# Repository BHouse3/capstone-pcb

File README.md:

# capstone-pcb

All files and documentation for PCB integration.

## Timeline

01/12/2026 - Created project repo and initial hierarchical KiCad structure. Found DFRobot's rp2350 module footprint.

01/13/2026 - Ethan created symbol for rp2350 module.

01/14/2026 - Created fuel gauge schematic with LC709203FQH-01TWG. Evaluating charging and voltage conversion methodology. 

01/15/2026 - Redesign of entire power subsystem. Utilizing TP4057 charger on board RP2350 module. DW01A + FS8205A protection circuitry. TPS61023 5V boost converter. BQ27441-G1 fuel gauge. Minimizes cost and number of components in power system. Ethan created L1 schematic with labels and wires for the symbol created on 01/13/2026. The symbol was also edited to correct labeling errors.

01/17/2026 - Power schematic starting point based on datasheet implementations. Will work to further verify. Changed MCU labels to global labels.

01/20/2026 - UI schematic finished. External connector symbols added. Hierarchical label issue. Washout detection schematic finished. Motor schematic finished.

01/22/2026 - Fixed critical polarity issue on flyback diodes. Hierarchical label assignment. Added missing I2C labels on power system

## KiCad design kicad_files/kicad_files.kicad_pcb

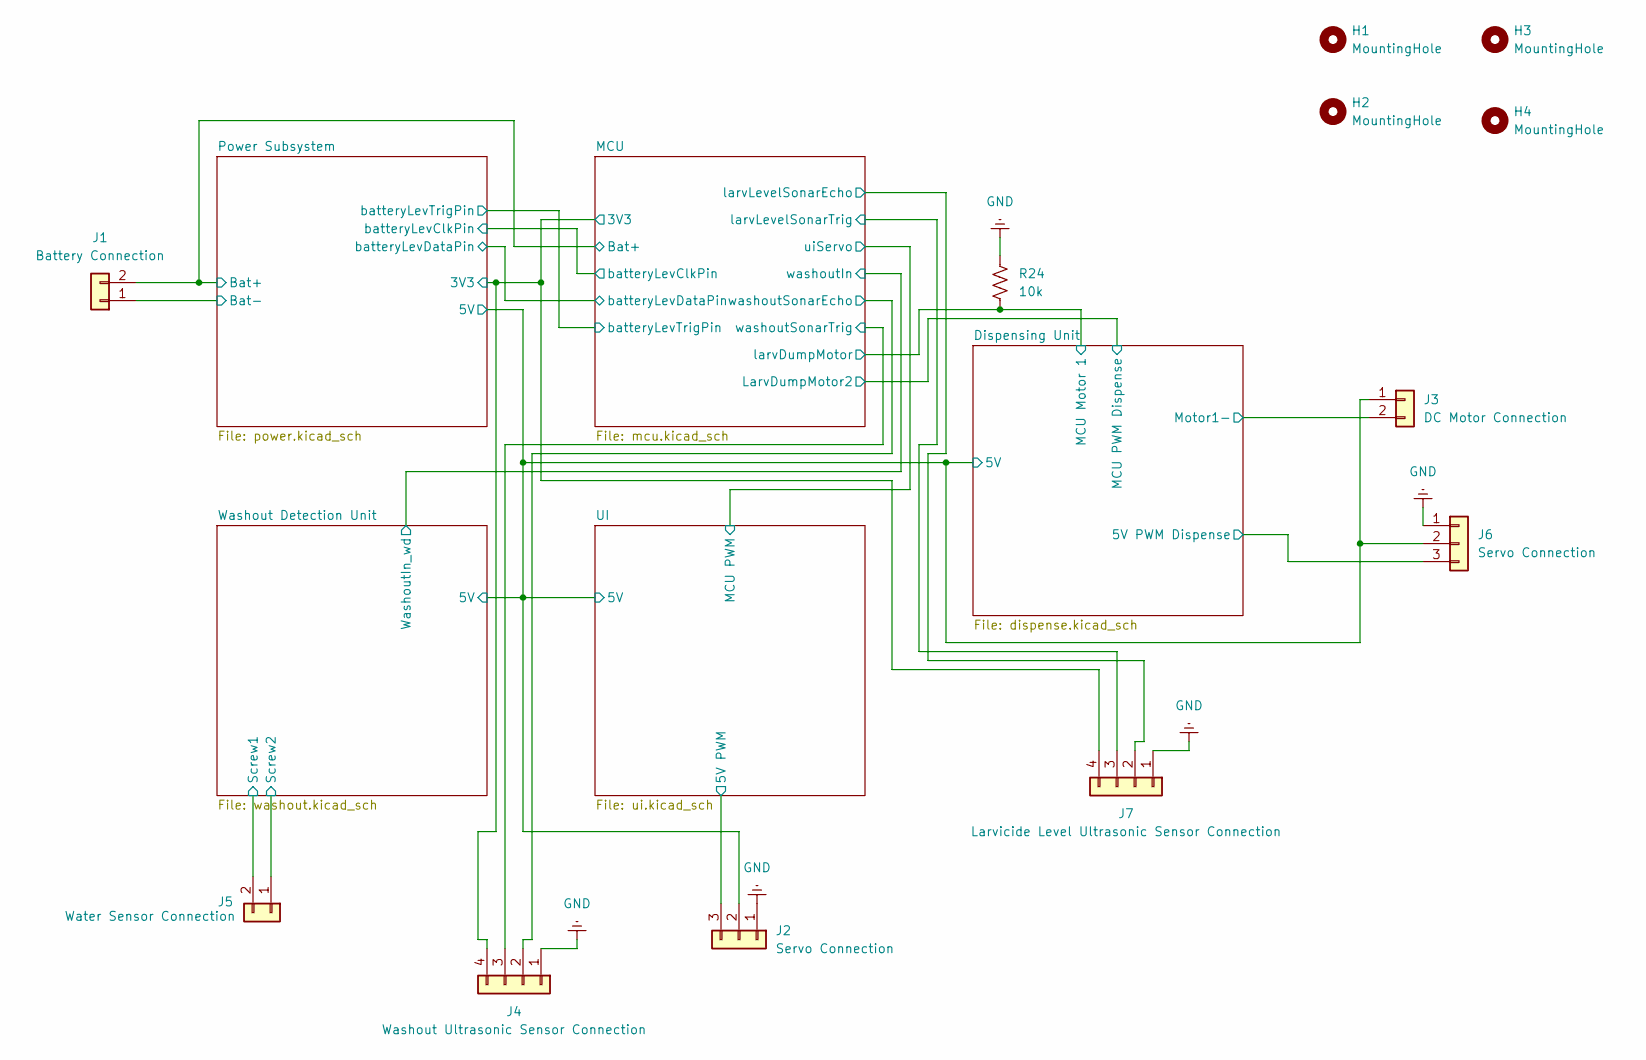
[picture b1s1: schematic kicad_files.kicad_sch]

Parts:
H1, H2, H3, H4: MountingHole; MountingHole_3.2mm_M3
J1: Battery Connection; JST_VH_B2P-VH_1x02_P3.96mm_Vertical
J2, J6: Servo Connection; PinHeader_1x03_P2.54mm_Vertical
J3: DC Motor Connection; JST_XH_B2B-XH-A_1x02_P2.50mm_Vertical
J4: Washout Ultrasonic Sensor Connection; JST_XH_B4B-XH-A_1x04_P2.50mm_Vertical
J5: Water Sensor Connection; JST_XH_B2B-XH-A_1x02_P2.50mm_Vertical
J7: Larvicide Level Ultrasonic Sensor Connection; JST_XH_B4B-XH-A_1x04_P2.50mm_Vertical
R24: 10k; R_1206_3216Metric_Pad1.30x1.75mm_HandSolder

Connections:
/Dispensing Unit/5V: J2.2, J3.1, J6.2; also elsewhere on the board
/Dispensing Unit/5V PWM Dispense: J6.3; also elsewhere on the board
/Dispensing Unit/MCU Motor 1: R24.2; also elsewhere on the board
/Dispensing Unit/Motor1-: J3.2; also elsewhere on the board
/MCU/3V3: J4.4, J7.4; also elsewhere on the board
/MCU/Bat+: J1.2; also elsewhere on the board
/MCU/larvLevelSonarEcho: J7.2; also elsewhere on the board
/MCU/larvLevelSonarTrig: J7.3; also elsewhere on the board
/MCU/washoutSonarEcho: J4.2; also elsewhere on the board
/MCU/washoutSonarTrig: J4.3; also elsewhere on the board
/Power Subsystem/Bat-: J1.1; also elsewhere on the board
/UI/5V PWM: J2.3; also elsewhere on the board
/Washout Detection Unit/Screw1: J5.2; also elsewhere on the board
/Washout Detection Unit/Screw2: J5.1; also elsewhere on the board
GND: J2.1, J4.1, J6.1, J7.1, R24.1; also elsewhere on the board

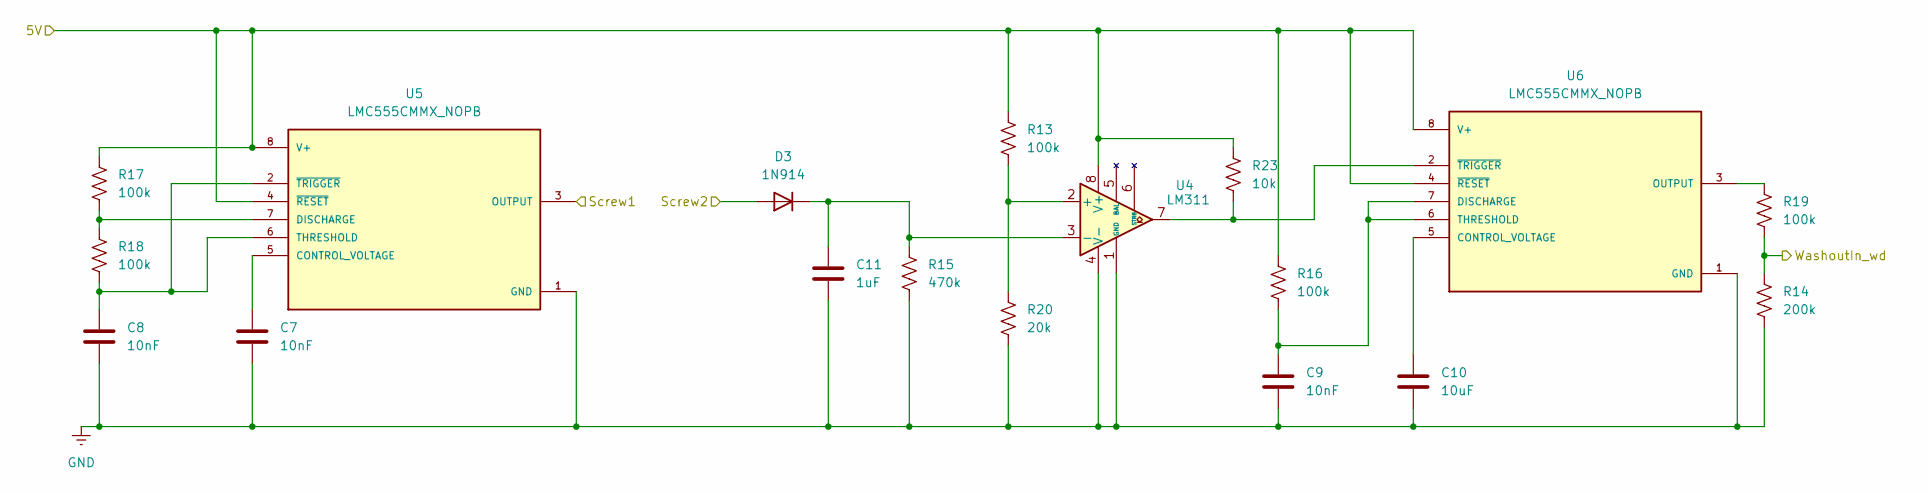
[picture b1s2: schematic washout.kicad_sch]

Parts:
C7, C8, C9: 10nF; C_1206_3216Metric_Pad1.33x1.80mm_HandSolder
C10: 10uF; C_1206_3216Metric_Pad1.33x1.80mm_HandSolder
C11: 1uF; C_1206_3216Metric_Pad1.33x1.80mm_HandSolder
D3: 1N914; D_DO-35_SOD27_P7.62mm_Horizontal
R13, R16, R17, R18, R19: 100k; R_1206_3216Metric_Pad1.30x1.75mm_HandSolder
R14: 200k; R_1206_3216Metric_Pad1.30x1.75mm_HandSolder
R15: 470k; R_1206_3216Metric_Pad1.30x1.75mm_HandSolder
R20: 20k; R_1206_3216Metric_Pad1.30x1.75mm_HandSolder
R23: 10k; R_1206_3216Metric_Pad1.30x1.75mm_HandSolder
U4: LM311; D8
U5, U6: LMC555CMMX_NOPB; D0008A_M; PARTREV M

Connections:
/Dispensing Unit/5V: R13.1, R16.1, R17.1, R23.1, U4.8 (V+), U5.4 (~RESET), U5.8 (V+), U6.4 (~RESET), U6.8 (V+); also elsewhere on the board
/MCU/washoutIn: R14.1, R19.2; also elsewhere on the board
/Washout Detection Unit/Screw1: U5.3 (OUTPUT); also elsewhere on the board
/Washout Detection Unit/Screw2: D3.2 (A); also elsewhere on the board
GND: C7.2, C8.2, C9.2, C10.2, C11.2, R14.2, R15.2, R20.2, U4.1 (GND), U4.4 (V-), U5.1 (GND), U6.1 (GND); also elsewhere on the board
unnamed: C11.1, D3.1 (K), R15.1, U4.3 (-)
unnamed: R13.2, R20.1, U4.2 (+)
unnamed: C7.1, U5.5 (CONTROL_VOLTAGE)
unnamed: R17.2, R18.1, U5.7 (DISCHARGE)
unnamed: C8.1, R18.2, U5.2 (~TRIGGER), U5.6 (THRESHOLD)
unnamed: C10.1, U6.5 (CONTROL_VOLTAGE)
unnamed: C9.1, R16.2, U6.6 (THRESHOLD), U6.7 (DISCHARGE)
unnamed: R19.1, U6.3 (OUTPUT)
unnamed: R23.2, U4.7, U6.2 (~TRIGGER)

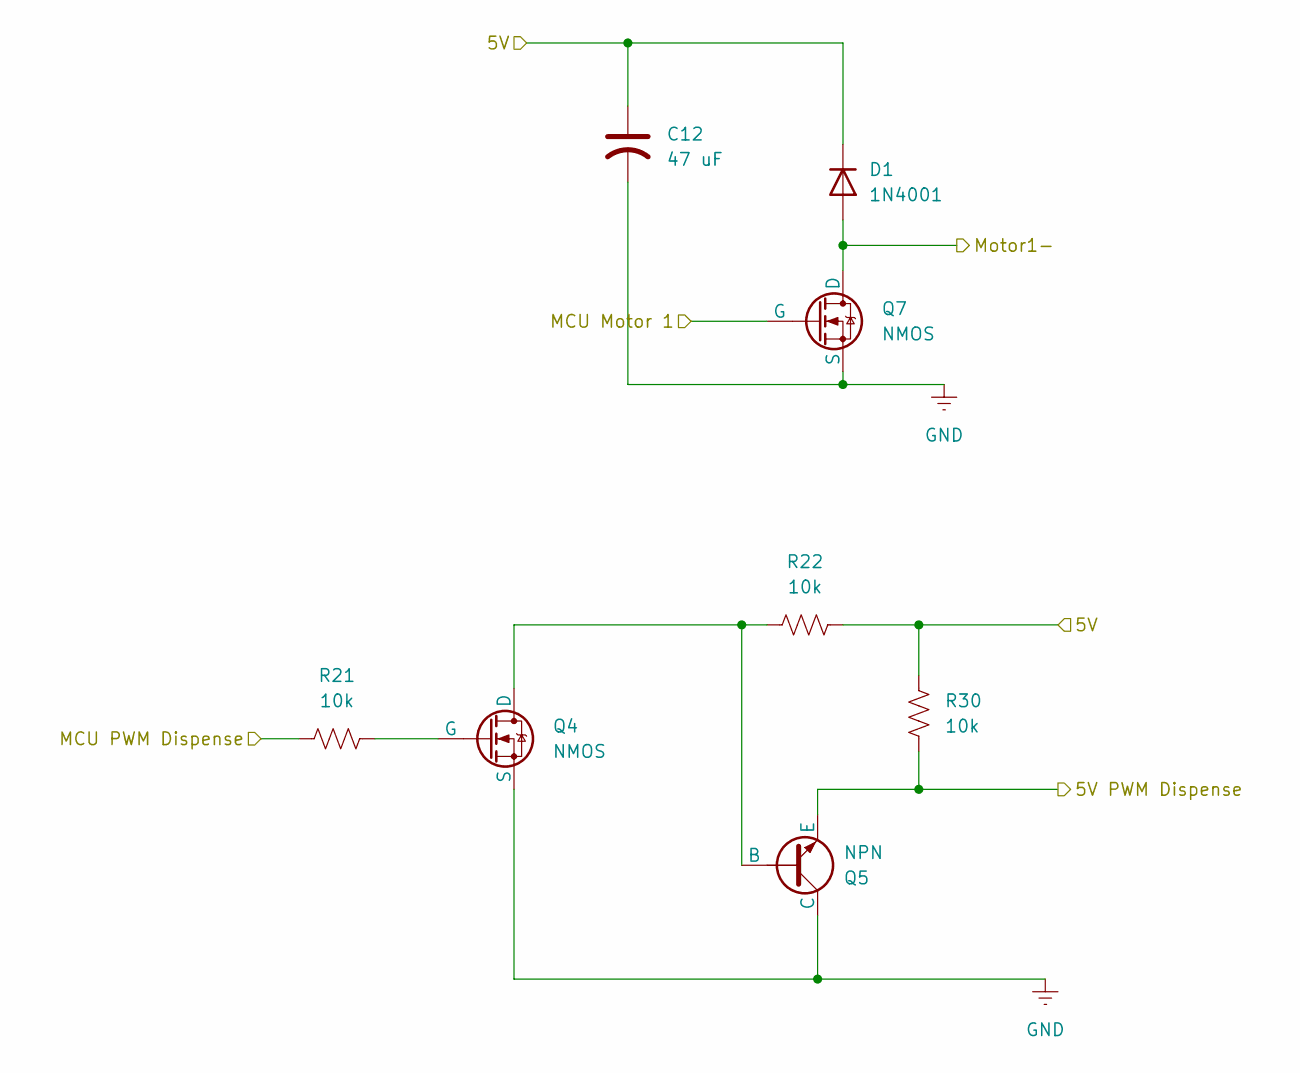
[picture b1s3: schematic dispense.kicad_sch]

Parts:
C12: 47 uF; CP_Radial_D5.0mm_P2.00mm
D1: 1N4001; D_DO-41_SOD81_P10.16mm_Horizontal
Q4: NMOS; SOT-323_SC-70
Q5: NPN; TSOT-23
Q7: NMOS; SOT-23-3
R21, R22, R30: 10k; R_1206_3216Metric_Pad1.30x1.75mm_HandSolder

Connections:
/Dispensing Unit/5V: C12.1, D1.1 (K), R22.1, R30.1; also elsewhere on the board
/Dispensing Unit/5V PWM Dispense: Q5.3 (E), R30.2; also elsewhere on the board
/Dispensing Unit/MCU Motor 1: Q7.2 (G); also elsewhere on the board
/Dispensing Unit/MCU PWM Dispense: R21.2; also elsewhere on the board
/Dispensing Unit/Motor1-: D1.2 (A), Q7.1 (D); also elsewhere on the board
GND: C12.2, Q4.3 (S), Q5.1 (C), Q7.3 (S); also elsewhere on the board
unnamed: Q4.1 (D), Q5.2 (B), R22.2
unnamed: Q4.2 (G), R21.1

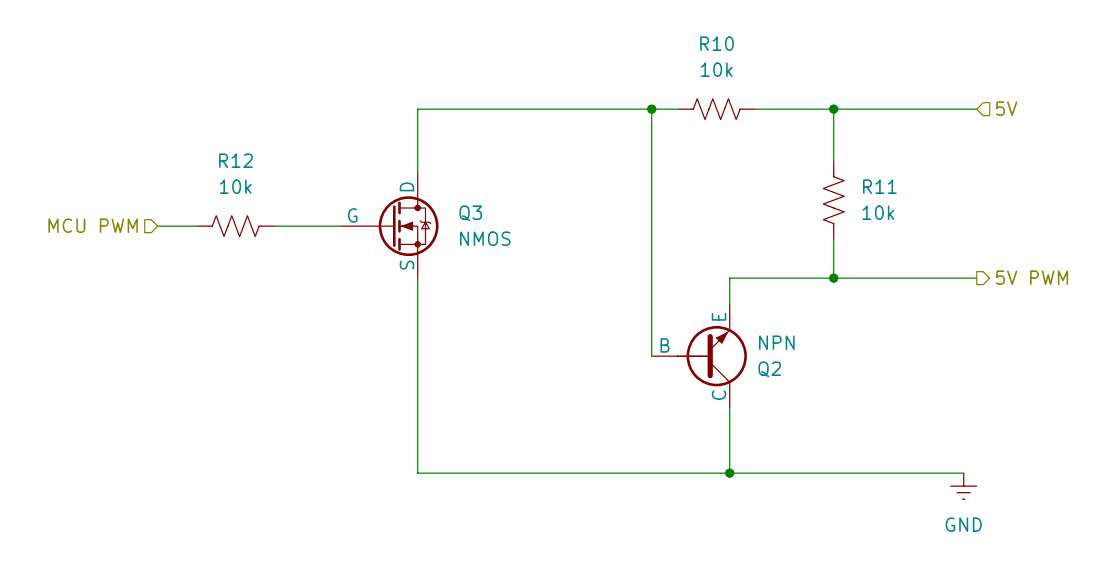
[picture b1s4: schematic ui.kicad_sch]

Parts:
Q2: NPN; TSOT-23
Q3: NMOS; SOT-323_SC-70
R10, R11, R12: 10k; R_1206_3216Metric_Pad1.30x1.75mm_HandSolder

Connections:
/Dispensing Unit/5V: R10.1, R11.1; also elsewhere on the board
/MCU/uiServo: R12.2; also elsewhere on the board
/UI/5V PWM: Q2.3 (E), R11.2; also elsewhere on the board
GND: Q2.1 (C), Q3.3 (S); also elsewhere on the board
unnamed: Q2.2 (B), Q3.1 (D), R10.2
unnamed: Q3.2 (G), R12.1

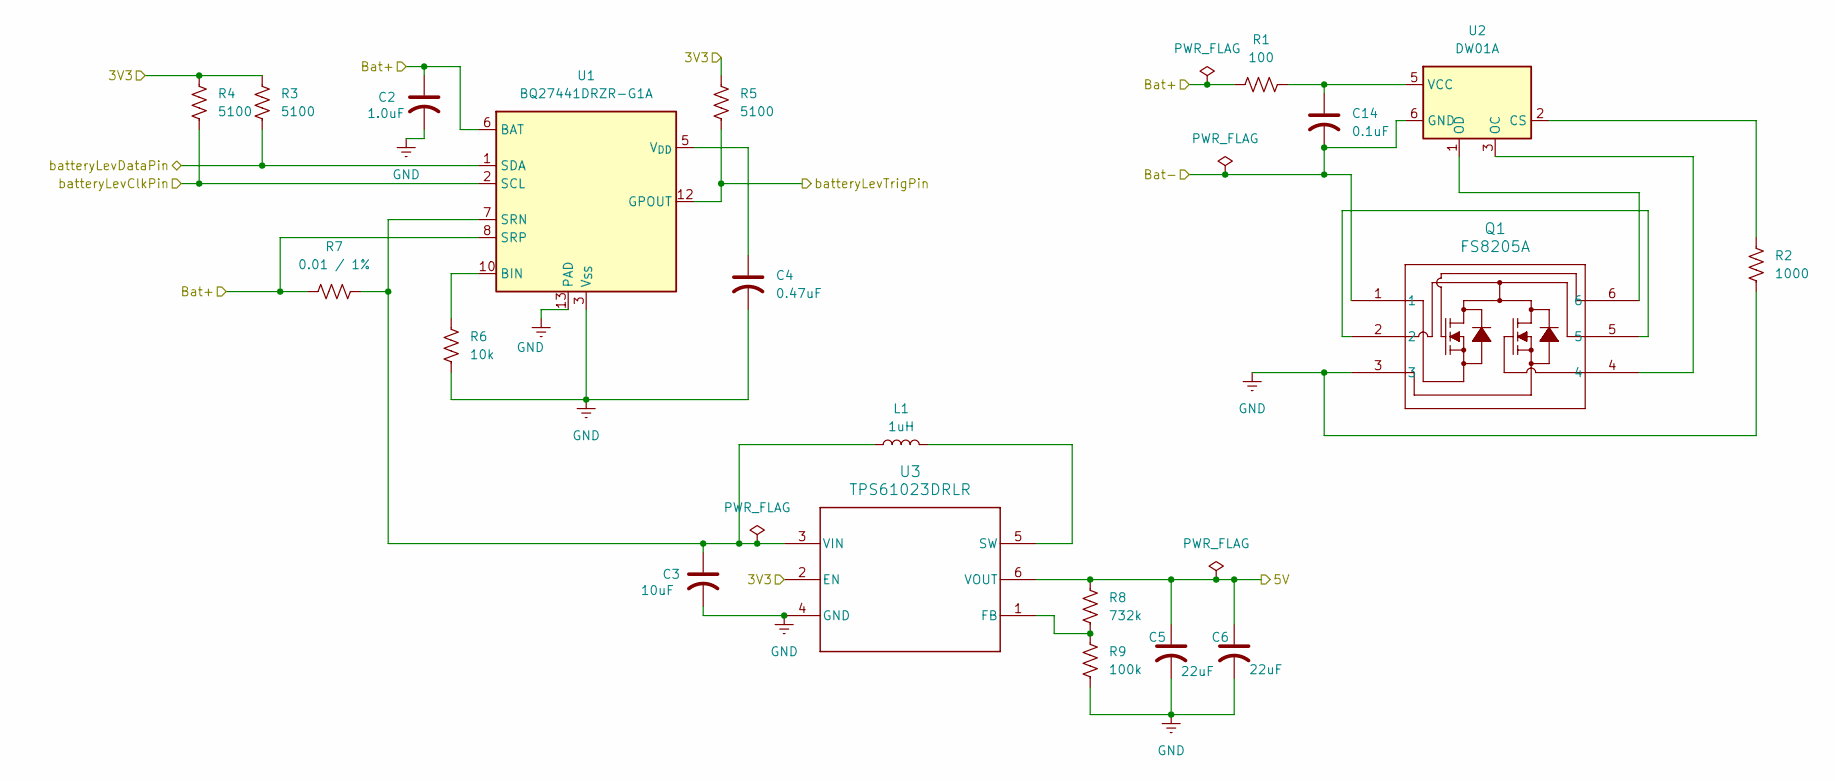
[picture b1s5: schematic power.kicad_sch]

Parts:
C2: 1.0uF; C_1206_3216Metric_Pad1.33x1.80mm_HandSolder
C3: 10uF; C_1206_3216Metric_Pad1.33x1.80mm_HandSolder
C4: 0.47uF; C_1206_3216Metric_Pad1.33x1.80mm_HandSolder
C5, C6: 22uF; CP_Radial_D5.0mm_P2.00mm
C14: 0.1uF; C_1206_3216Metric_Pad1.33x1.80mm_HandSolder
L1: 1uH; L_1008_2520Metric_Pad1.43x2.20mm_HandSolder
Q1: FS8205A; SOT-23-6L_TCP
R1: 100; R_1206_3216Metric_Pad1.30x1.75mm_HandSolder
R2: 1000; R_1206_3216Metric_Pad1.30x1.75mm_HandSolder
R3, R4, R5: 5100; R_1206_3216Metric_Pad1.30x1.75mm_HandSolder
R6: 10k; R_1206_3216Metric_Pad1.30x1.75mm_HandSolder
R7: 0.01 / 1%; R_1206_3216Metric_Pad1.30x1.75mm_HandSolder
R8: 732k; R_1206_3216Metric_Pad1.30x1.75mm_HandSolder
R9: 100k; R_1206_3216Metric_Pad1.30x1.75mm_HandSolder
U1: BQ27441DRZR-G1A; Texas_S-PDSO-N12
U2: DW01A; SOT-23-6
U3: TPS61023DRLR; DRL0006A

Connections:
/Dispensing Unit/5V: C5.1, C6.1, R8.1, U3.6 (VOUT); also elsewhere on the board
/MCU/3V3: R3.1, R4.1, R5.1, U3.2 (EN); also elsewhere on the board
/MCU/Bat+: C2.1, R1.2, R7.2, U1.6 (BAT), U1.8 (SRP); also elsewhere on the board
/MCU/batteryLevClkPin: R4.2, U1.2 (SCL); also elsewhere on the board
/MCU/batteryLevDataPin: R3.2, U1.1 (SDA); also elsewhere on the board
/MCU/batteryLevTrigPin: R5.2, U1.12 (GPOUT); also elsewhere on the board
/Power Subsystem/Bat-: C14.2, Q1.1, U2.6 (GND); also elsewhere on the board
GND: C2.2, C3.2, C4.2, C5.2, C6.2, Q1.3, R2.2, R6.2, R9.2, U1.3 (V_{SS}), U1.13 (PAD), U3.4 (GND); also elsewhere on the board
unnamed: Q1.2, Q1.5
unnamed: R6.1, U1.10 (BIN)
unnamed: C3.1, L1.1, R7.1, U1.7 (SRN), U3.3 (VIN)
unnamed: C4.1, U1.5 (V_{DD})
unnamed: R2.1, U2.2 (CS)
unnamed: Q1.4, U2.3 (OC)
unnamed: Q1.6, U2.1 (OD)
unnamed: C14.1, R1.1, U2.5 (VCC)
unnamed: R8.2, R9.1, U3.1 (FB)
unnamed: L1.2, U3.5 (SW)

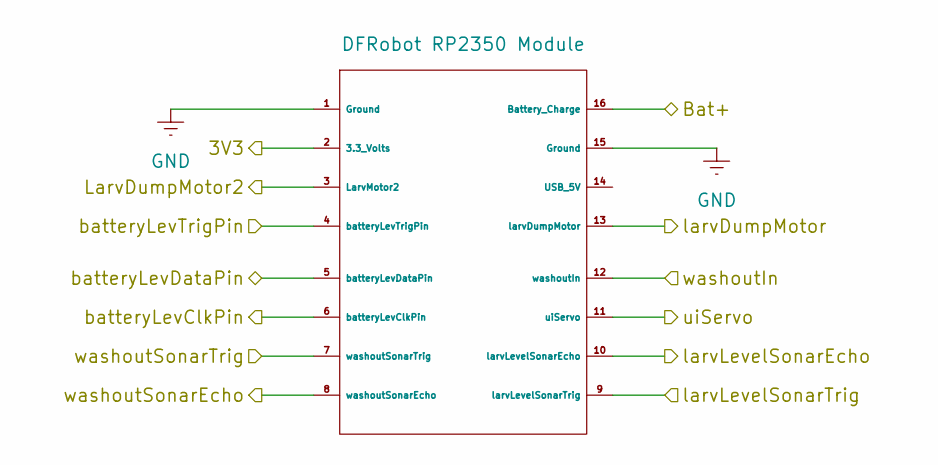
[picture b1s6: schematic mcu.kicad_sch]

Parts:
.1: DFRobot RP2350 Module; DFR1188-DIP

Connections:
unnamed: .1.1 (Ground), .1.15 (Ground)

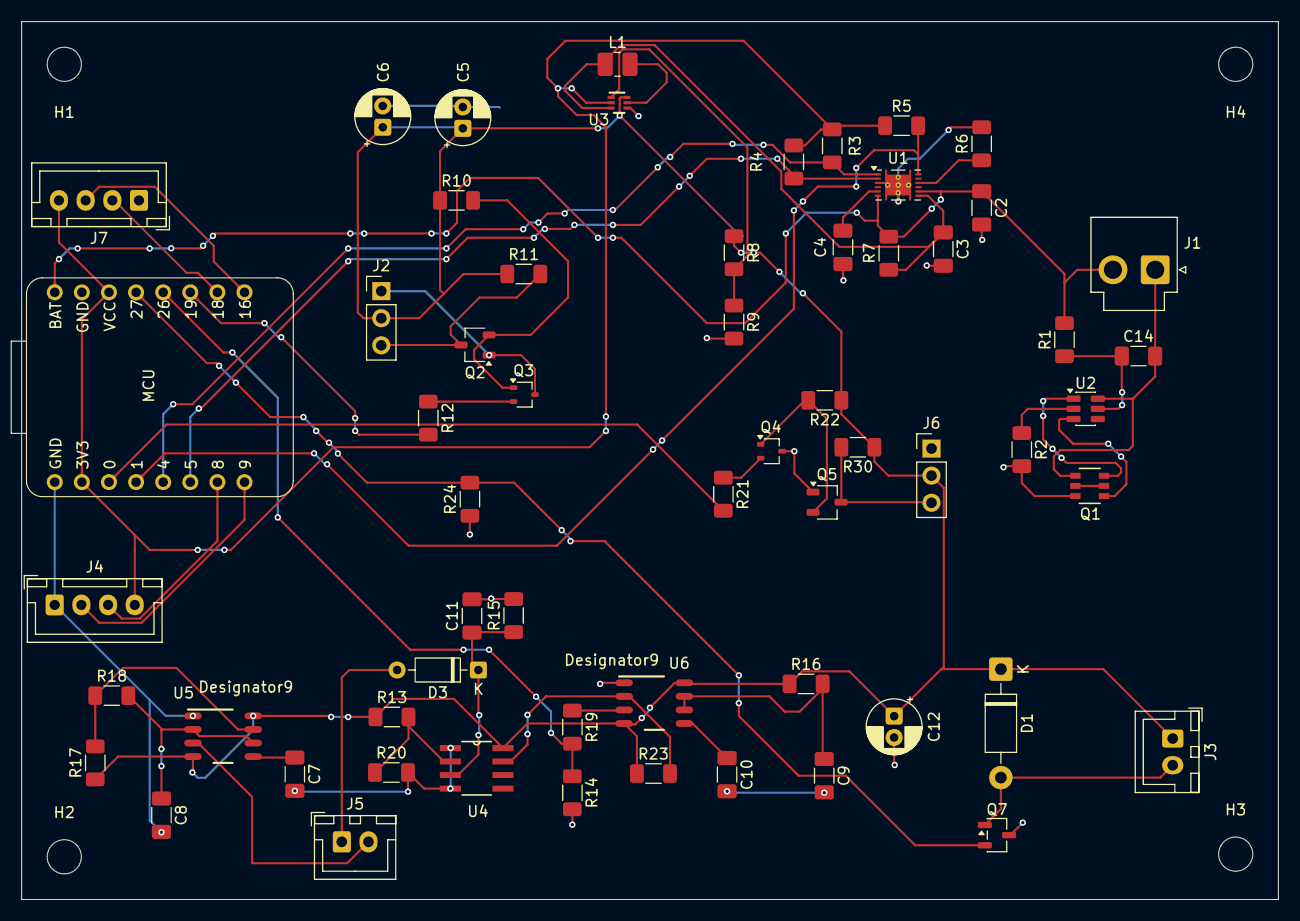
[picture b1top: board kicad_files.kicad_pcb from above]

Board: 2 copper layers, 117.8 x 82.2 mm, 64 parts (0 on the bottom side), 44 nets.

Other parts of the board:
MCU: DFRobot RP2350 Module; DFR1188-DIP

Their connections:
/Dispensing Unit/MCU Motor 1: MCU.13 (larvDumpMotor); also elsewhere on the board
/Dispensing Unit/MCU PWM Dispense: MCU.3 (LarvMotor2); also elsewhere on the board
/MCU/3V3: MCU.2 (3.3_Volts); also elsewhere on the board
/MCU/Bat+: MCU.16 (Battery_Charge); also elsewhere on the board
/MCU/batteryLevClkPin: MCU.6 (batteryLevClkPin); also elsewhere on the board
/MCU/batteryLevDataPin: MCU.5 (batteryLevDataPin); also elsewhere on the board
/MCU/batteryLevTrigPin: MCU.4 (batteryLevTrigPin); also elsewhere on the board
/MCU/larvLevelSonarEcho: MCU.10 (larvLevelSonarEcho); also elsewhere on the board
/MCU/larvLevelSonarTrig: MCU.9 (larvLevelSonarTrig); also elsewhere on the board
/MCU/uiServo: MCU.11 (uiServo); also elsewhere on the board
/MCU/washoutIn: MCU.12 (washoutIn); also elsewhere on the board
/MCU/washoutSonarEcho: MCU.8 (washoutSonarEcho); also elsewhere on the board
/MCU/washoutSonarTrig: MCU.7 (washoutSonarTrig); also elsewhere on the board
GND: MCU.1 (Ground), MCU.15 (Ground); also elsewhere on the board

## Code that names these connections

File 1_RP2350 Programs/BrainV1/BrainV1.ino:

//Project Name: Drain Defenders Processor Code
//Author: Ethan Conrad
//Reason: Control Drain Defenders Device
//Class: EE/CPE 490/491
//History: 10/30/2025 - Start Date
//         11/03/2025 - Adjusted pin definitions to match RP2350 actual pin layout, changed washoutIn to be a
//                      a digital input instead of analog to allow for interrupt usage, and added UI servo motor
//                      logic to work with one servo instead of two, and added servoCheck function to check
//                      servo states for the "both" state
//         11/04/2025 - Asjusted pin definitions to allow battery interrrupt sense to have I2C compatibility
//         11/10/2025 - Changed larvDumpMotor to larvDumpMotor due to realzing the RP2350 pins cannot supply in
//                      rush current needed to turn motor sufficiently. Then updated all code relevant to motor
//                      to digital commands to support MOSFET circuit logic
//         11/11/2025 - Adjusted duration of the low power sleep to be 5 minutes or 300000 ms
//         11/24/2025 - Changed Washout Sensor Interupt to falling edge based on results from testing script
//         12/02/2025 - Included Adafuit library and associated code/logic to enable I2C communication with Power
//                      Distribution subsystem
//         12/03/2025 - B.H.: Added I2C initialization and LC709203F/interrupt communication
//         12/08/2025 - added in set clock and data initialization code to fix I2C errors
//
//Purpose: To create a program that can be used to control the device that the Drain Defenders design for their
//             project sponsor Todd Montgomery. This device should be able to detect water flowing into a
//             water basin and dispense larvicide as needed. This code shall be able to receive and interface
//             with all necessary IO's from the different subsystems and process them correctly.
//////////////////////////////////////////////////////////////////////////////////////////////////////////////////
#include <Servo.h>
#include <Wire.h>
#include "Adafruit_LC709203F.h"

// === Pin Definitions ===
const int washoutIn = 26;       // Digital pin to detect high signal (interrupt) from washout sensor
const int washoutSonarTrig = 8;              // Washout Sonar trigger pin
const int washoutSonarEcho = 9;              // Washout Sonoar echo pin
const int larvLevelSonarTrig = 16;              // Larvicide Level trigger pin (sonar)
const int larvLevelSonarEcho = 18;              // Larvicide Level echo pin (sonar)
const int larvDumpMotor = 27;               // Larvicide Level Dump Motor (PWM pin for N-Type MOSFET)
const int uiServo = 19;                // UI Battery Control Servo Motor
const int batteryLevTrigPin = 1;       // Battery Level Digital Input (interrupt)
const int batteryLevClkPin = 5;       // Battery Level Digital Input (interrupt)
const int batteryLevDataPin = 4;       // Battery Level Digital Input (interrupt)

// === Objects and Globals ===
Servo servoMotor; //Create Servo motor
Adafruit_LC709203F lc; //Create Fuel guage object
volatile bool washoutTrigger = false;   // boolean for washout interrupt trigger
volatile bool batteryTrigger = false; //boolean for battery interrupt trigger
float previousDistance = -1.0;         // Store last distance for washoutSonar, initialized to -1 for system boot
const float larvicideThreshold = 40.0;    // Preprogrammed value for larvicide level
volatile int larveCheck = 0; // Store checking variable for larvicide level
volatile int battCheck = 0; // Store checking variable for battery level
// === Utility: Measure distance from an HC-SR04-style sensor ===
float getSonarDistance(int trigPin, int echoPin) {
  digitalWrite(trigPin, LOW);
  delayMicroseconds(2);
  digitalWrite(trigPin, HIGH);
  delayMicroseconds(10);
  digitalWrite(trigPin, LOW);// Writing Sequences for gaining
  long duration = pulseIn(echoPin, HIGH, 30000); // measure timeout in µs
  Serial.println(duration);
  float distance = (duration * 0.0343) / 2.0;      // ocnvert distance to cm
  return distance;//return distance
}//end getSonarDistance

// === Interrupt handlers ===
//Washout Interupt function
void washoutInterruptHandler() {//removed IRAM_ATTR
Serial.println("Washout Sensed");
  washoutTrigger = true;// flip boolean for execution in main loop
}//end washoutInterruptHandler

void batteryDigitalInterruptHandler() {//removed IRAM_ATTR
Serial.println("Battery Low Sensed");
    batteryTrigger = true;// flip boolean for execution in main loop
}//end batteryDigitialInterruptHandler

// === Utility: Move Servo to Final State if conditon given ===
void servoCheck() {
      if(larveCheck == 1 && battCheck == 1){
            servoMotor.write(100);
            larveCheck = 0;
            //battCheck = 0;
      }//end if
}//end servo check

// === Setup ===
void setup() {
  // Serial optional for debugging
  Serial.begin(9600);
  delay(2000);
  // Configure all pins
  pinMode(washoutIn, INPUT);
  pinMode(washoutSonarTrig, OUTPUT);
  pinMode(washoutSonarEcho, INPUT);
  pinMode(larvLevelSonarTrig, OUTPUT);
  pinMode(larvLevelSonarEcho, INPUT);
  pinMode(larvDumpMotor, OUTPUT);
  digitalWrite(larvDumpMotor, LOW);//Ensure MOSFET is closed at start
  pinMode(batteryLevTrigPin, INPUT_PULLUP);
  Serial.println("Begin Initialize");
 
  Wire.setSDA(batteryLevDataPin);
  Wire.setSCL(batteryLevClkPin);
  Wire.setClock(10000);
  Wire.begin();
  // Attach battery servo to project
  servoMotor.attach(uiServo);
  servoMotor.write(0);  // Start at 0%
  // Set interrupts
  attachInterrupt(digitalPinToInterrupt(batteryLevTrigPin), batteryDigitalInterruptHandler, FALLING);
  attachInterrupt(digitalPinToInterrupt(washoutIn), washoutInterruptHandler, FALLING);
  // Analog interrupt: use pin change or poll threshold
  washoutTrigger = false;
  batteryTrigger = false;
  //
  while (!lc.begin(&Wire)) {
    Serial.println(F("Couldnt find Adafruit LC709203F?\nMake sure a battery is plugged in!"));
    delay(10000);
  }
  Serial.println(F("Found LC709203F"));
  lc.setThermistorB(3950);
  lc.setPackSize(LC709203F_APA_3000MAH);
  lc.setAlarmRSOC(20);

  // Low power setup (optional: external libs like LowPower.h can deepen sleep)
  Serial.println("System initialized, entering low power wait...");
}//end steup function

// === Main loop ===
void loop() {
  // Check if battery is sensed to be low (interrupt trigger)
  if (batteryTrigger) {
    batteryTrigger = false;// reset boolean
    servoMotor.write(33);  // Move servo to 100%
    battCheck = 1;
    delay(1000);//give it time to move
    servoCheck();
  }
  // Check if washout event is sensed (interrupt trigger)
  if (washoutTrigger) {
    washoutTrigger = false; //reset boolean
    //Measure distance from device to water in water basin
    float devToWaterDist = getSonarDistance(washoutSonarTrig, washoutSonarEcho);//store distance in distance variable
    Serial.print("Sonar1 distance: "); Serial.println(devToWaterDist);//debug statement to print data
    if (previousDistance < 0 || abs(devToWaterDist - previousDistance) > 1.0) { // Change detected
      digitalWrite(larvDumpMotor, HIGH); // Run motor full power
      Serial.print("Dispensing Larvicide");
      delay(4000);               // 2 seconds, need to edit for how long a scoop is
      digitalWrite(larvDumpMotor, LOW);   // Stop motor
      // Measure larivicde level
      float sensToLarvDistance = getSonarDistance(larvLevelSonarTrig, larvLevelSonarEcho);//find distance from sonar to larvicide level
      Serial.print("Sonar2 distance: "); Serial.println(sensToLarvDistance);//debug statement to print data
      if (sensToLarvDistance < larvicideThreshold) {//If larvicide is less than threshold indicate it on the UI
         servoMotor.write(66);
         delay(1000);
         larveCheck = 1;
         servoCheck();
      }//end if ()
    }//end if (dispense)
    previousDistance = devToWaterDist;//update and store new distance
  }//end if
  
  // === Low Power Wait ===
  //delay(300000); // short delay; replace with LowPower.sleep() for deep sleep, in ms,
  Serial.println("Sleeping");// This and below delay statement for debugging
  delay(1000);
}

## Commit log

2026-01-13 Initial hierarchical project structure with a custom symbol library created.
2026-01-13 DFRobot RP2350 kicad files. Used for footprint assignment
2026-01-13 Initial repo setup
2026-01-13 Hello I have modified stuff
2026-01-14 Kicad files for TPS63021 buck boost regulator IC
2026-01-14 Completed fuel gauge schematic based on application guidance provided in the LC709203F datasheet.
2026-01-15 cringe
2026-01-15 FS8205A kicad files
2026-01-15 TPS61023 kicad files
2026-01-15 Revamped power subsystem design
2026-01-15 Deleting unnecessary files
2026-01-17 Protection portion of power subsystem
2026-01-18 Initial power system implementation
2026-01-20 UI schematic and external connectors
2026-01-20 LMC555 symbol and footprint files
2026-01-20 UI, washout detection, motor schematics finished
2026-01-22 Hierarchical labels finished. Flyback diode issue fixed. I2C pins added
2026-01-22 Ben Cant work GitHub
2026-01-22 LM311 kicad files from TI
2026-01-22 Partial footprint assignment
2026-01-25 ERC errors cleaned. Hierarchical wiring finished. PWM converter change. Motor driver change.
2026-01-25 Updated schematic pdf
2026-02-02 minor changes
2026-02-19 ben pls use
2026-02-20 Footprint assignment finished
2026-02-26 Housing and Dispensing Subsystem Models
2026-03-03 First pass floorplan and routing
2026-03-03 First pass revisions
2026-03-03 Second pass routing and floorplan
2026-03-03 Floorplan revisions
2026-03-03 Schematic and Footprint error fix
2026-04-27 final commit
